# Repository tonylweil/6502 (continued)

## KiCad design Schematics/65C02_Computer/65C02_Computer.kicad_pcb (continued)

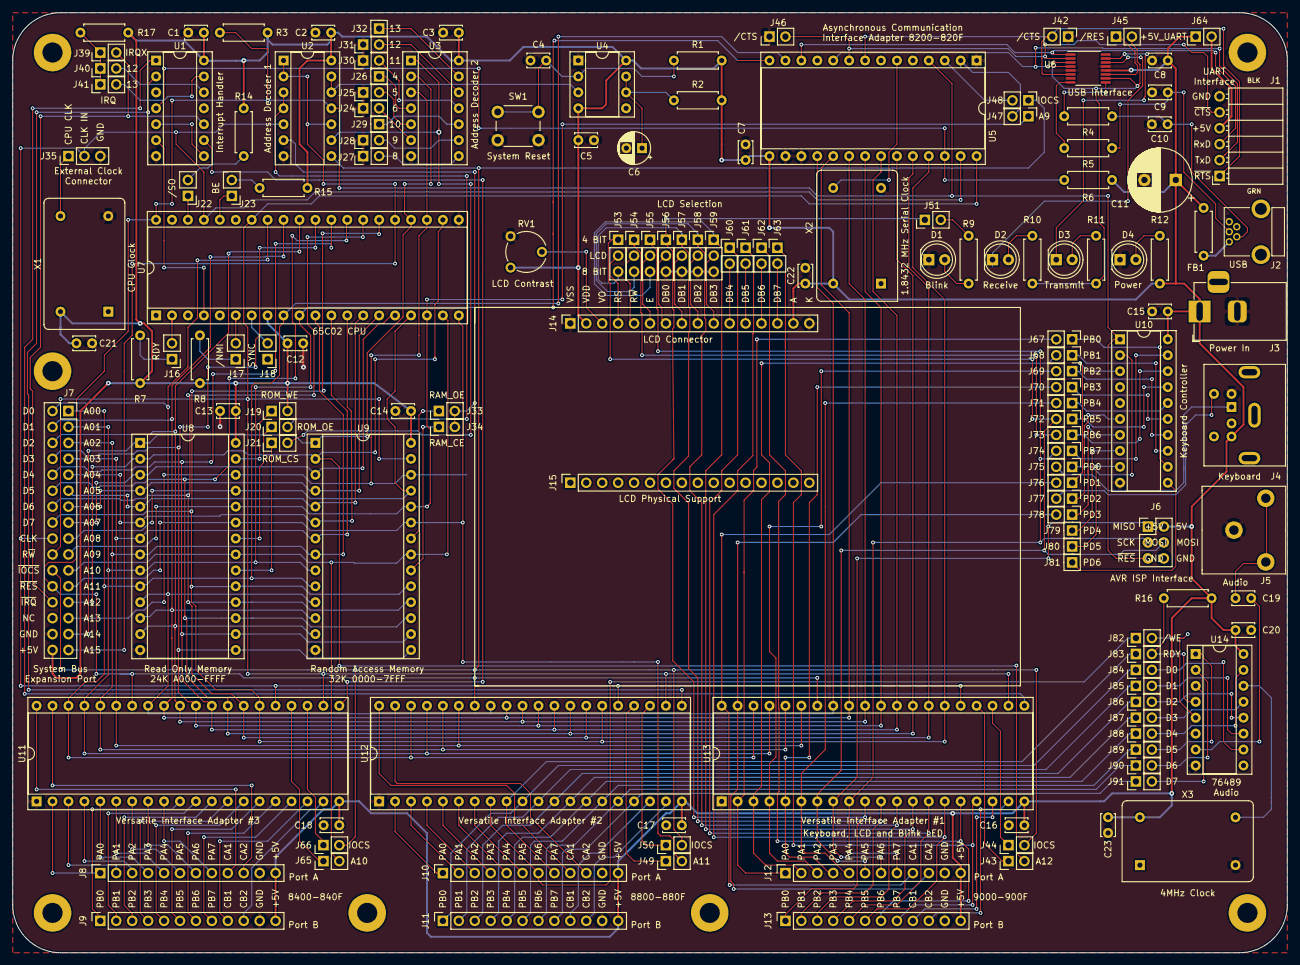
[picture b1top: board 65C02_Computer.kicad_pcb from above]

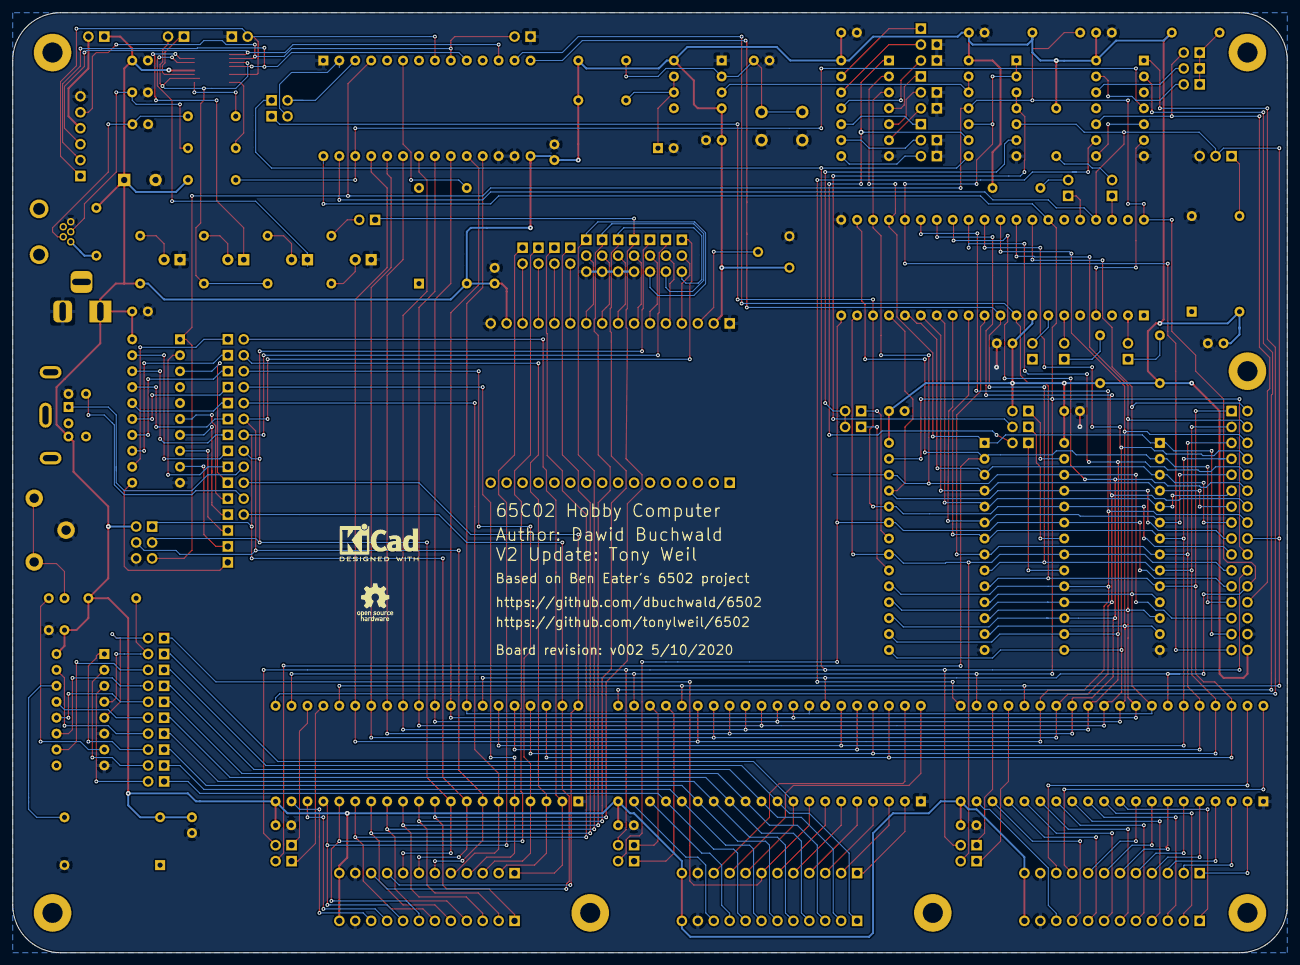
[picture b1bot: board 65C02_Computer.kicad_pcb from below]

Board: 2 copper layers, 203.2 x 149.9 mm, 159 parts (2 on the bottom side), 200 nets.

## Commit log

2020-05-10 Updated schematics and board files to V002
2020-05-10 Added datasheets for V002
2020-05-10 Update files to v002
2020-05-10 Updated for v002
2020-05-12 Update for v002
2020-05-15 Update README v2
